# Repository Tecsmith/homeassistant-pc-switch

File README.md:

#  HA PC Switch

**Automate power on your PC using [ESPHome](https://github.com/esphome/esphome) or [Tasmota](https://github.com/arendst/Tasmota), and integrated into [Home Assistant](https://www.home-assistant.io/).**

## About

For more, visit the project page here: https://tecsmith.github.io/homeassistant-pc-switch/

## Assets:

* [Schematic PDF](docs/ha-pc-switch-revB.pdf)

---

Made with &#x1F499; by .

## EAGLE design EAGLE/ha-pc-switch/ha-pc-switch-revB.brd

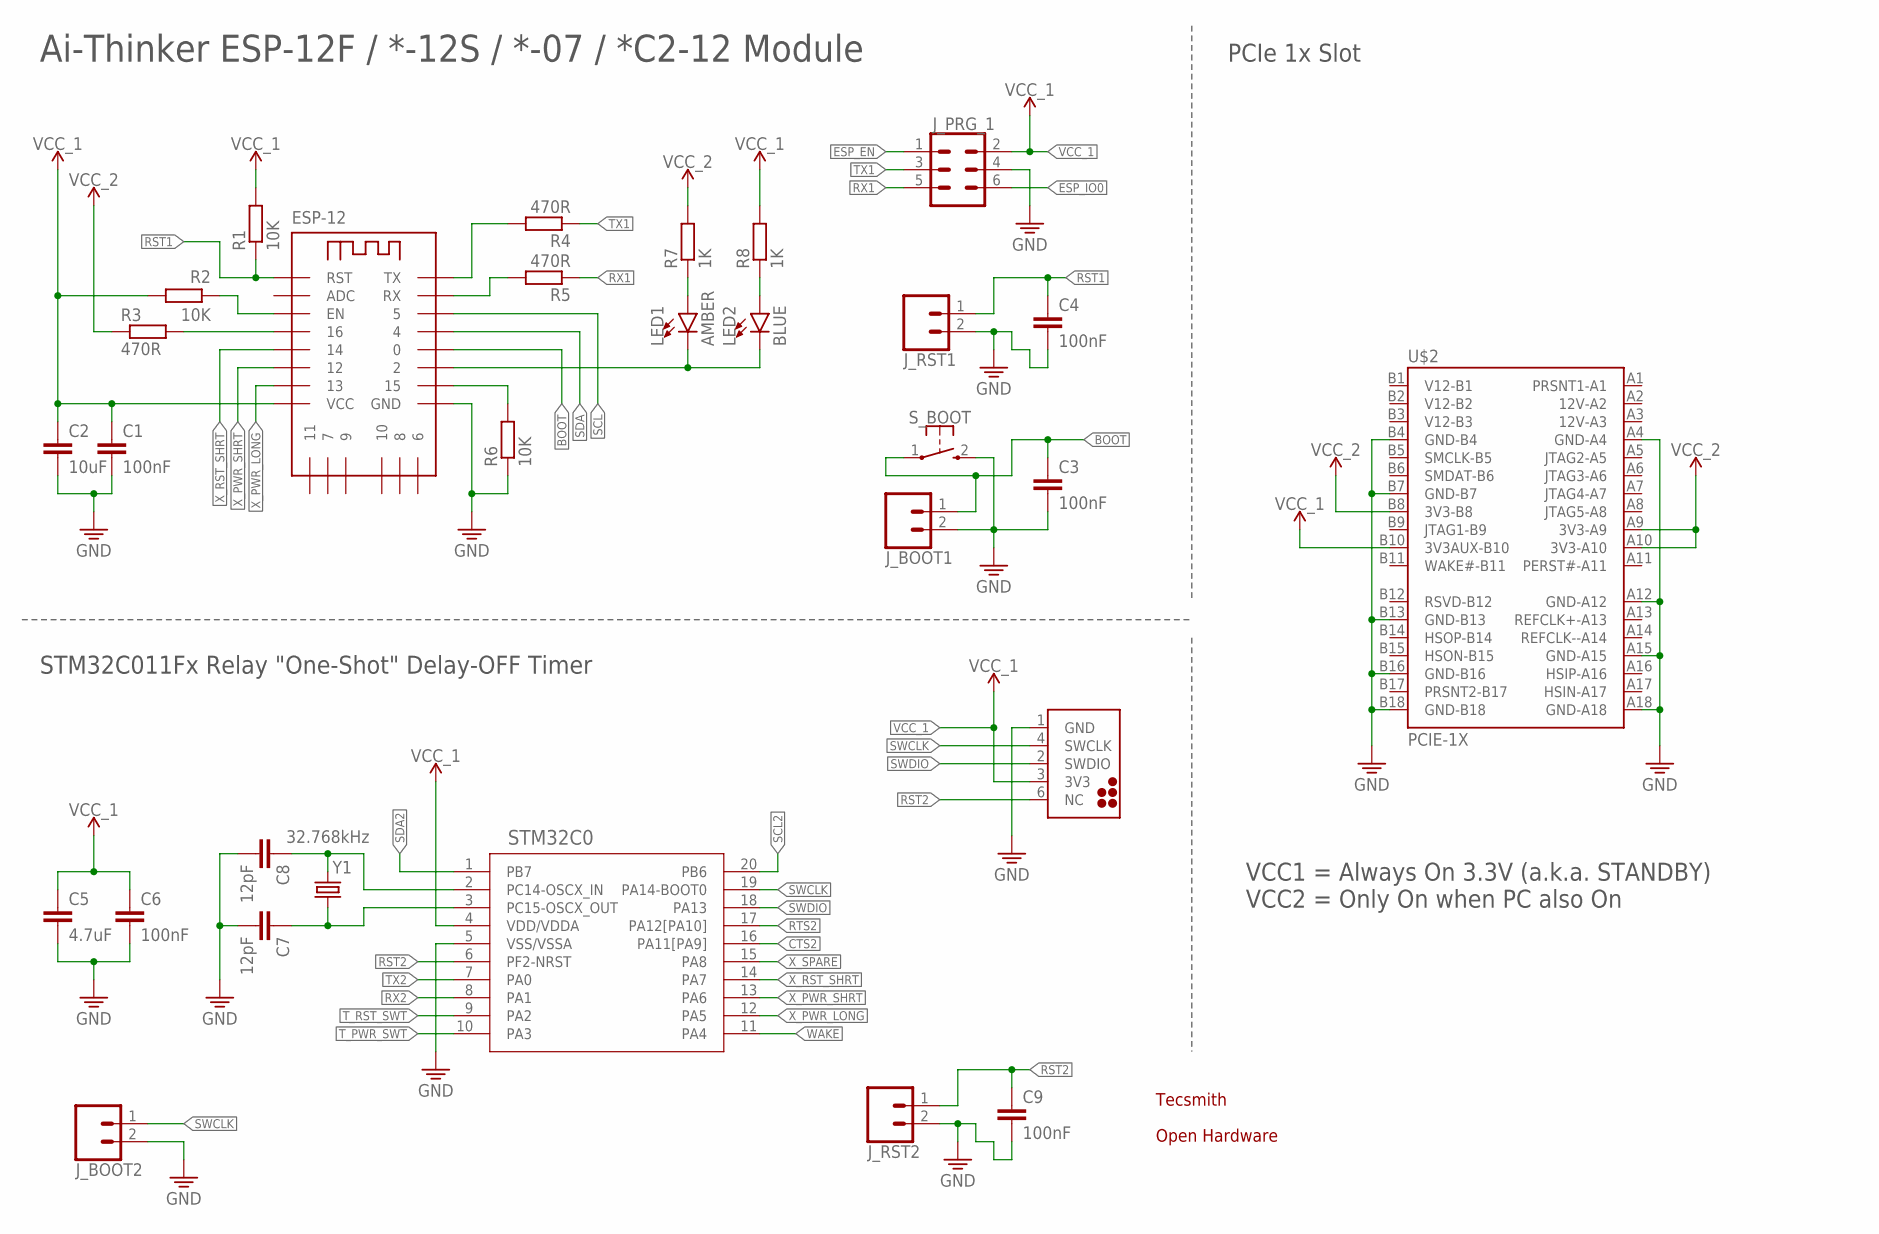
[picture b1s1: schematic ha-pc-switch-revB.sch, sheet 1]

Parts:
C1, C3, C4, C6, C9: 100nF; C0603
C2: 10uF; C0603
C5: 4.7uF; C0603
C7, C8: 12pF; C0603
ESP-12: ESPRESSIF-ESP-12F&ESMD; ESP8266-ESP-12E
J_BOOT1, J_BOOT2: CONN_021X02_NO_SILK; 1X02_NO_SILK
J_PRG2: NUCLEO_HEADER; NUCLEO
J_PRG_1: CONN_03X2NO_SILK; 2X3-NS
J_RST1, J_RST2: CONN_021X02_NO_SILK; 1X02_NO_SILK
LED1: AMBER; LED-0603
LED2: BLUE; LED-0603
LOGO1: OSHW-LOGOM; OSHW-LOGO-M
R1, R2, R6: 10K; R0603
R3, R4, R5: 470R; R0603
R7, R8: 1K; R0603
STM32C0: STM32C011FTSSOP20_STM-M; TSSOP20-M
S_BOOT: MOMENTARY-SWITCH-SPST-1; SKRKAEE020
U$1: TECSMITH-LOGOLONG; TECSMITH-NAME
U$2: PCIE-1X
Y1: 32.768kHz; CRYSTAL-SMD-3.2X1.5MM

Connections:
BOOT: C3.1, ESP-12.GPIO0 (0), J_BOOT1.1, S_BOOT.1
CTS2: STM32C0.16 (PA11[PA9])
ESP_EN: ESP-12.EN, J_PRG_1.1, R2.2
ESP_IO0: J_PRG_1.6
GND: C1.2, C2.2, C3.2, C4.2, C5.2, C6.2, C7.2, C8.2, C9.2, ESP-12.GND, J_BOOT1.2, J_BOOT2.2, J_PRG2.1 (GND), J_PRG_1.4, J_RST1.2, J_RST2.2, R6.1, STM32C0.5 (VSS/VSSA), S_BOOT.2 (3), U$2.A4 (GND-A4), U$2.A12 (GND-A12), U$2.A15 (GND-A15), U$2.A18 (GND-A18), U$2.B4 (GND-B4), U$2.B7 (GND-B7), U$2.B13 (GND-B13), U$2.B16 (GND-B16), U$2.B18 (GND-B18); also elsewhere on the board
unnamed: ESP-12.GPIO16 (16), R3.2
unnamed: LED2.A, R8.1
unnamed: C8.1, STM32C0.2 (PC14-OSCX_IN), Y1.P$2 (2)
unnamed: C7.1, STM32C0.3 (PC15-OSCX_OUT), Y1.P$1 (1)
unnamed: LED1.A, R7.1
unnamed: ESP-12.RXD0 (RX), R5.2
unnamed: ESP-12.GPIO2 (2), LED1.C, LED2.C
unnamed: ESP-12.TXD0 (TX), R4.2
unnamed: ESP-12.GPIO15 (15), R6.2
RST1: C4.1, ESP-12.RST, J_RST1.1, R1.1
RST2: C9.1, J_PRG2.6 (NC), J_RST2.1, STM32C0.6 (PF2-NRST)
RTS2: STM32C0.17 (PA12[PA10])
RX1: J_PRG_1.5, R5.1
RX2: STM32C0.8 (PA1)
SCL: ESP-12.GPIO5 (5); also elsewhere on the board
SCL2: STM32C0.20 (PB6)
SDA: ESP-12.GPIO4 (4); also elsewhere on the board
SDA2: STM32C0.1 (PB7)
SWCLK: J_BOOT2.1, J_PRG2.4 (SWCLK), STM32C0.19 (PA14-BOOT0)
SWDIO: J_PRG2.2 (SWDIO), STM32C0.18 (PA13)
TX1: J_PRG_1.3, R4.1
TX2: STM32C0.7 (PA0)
T_PWR_SWT: STM32C0.10 (PA3); also elsewhere on the board
T_RST_SWT: STM32C0.9 (PA2); also elsewhere on the board
VCC_1: C1.1, C2.1, C5.1, C6.1, ESP-12.VCC, J_PRG2.3 (3V3), J_PRG_1.2, R1.2, R2.1, R8.2, STM32C0.4 (VDD/VDDA), U$2.B10 (3V3AUX-B10); also elsewhere on the board
VCC_2: R3.1, R7.2, U$2.A9 (3V3-A9), U$2.A10 (3V3-A10), U$2.B8 (3V3-B8)
WAKE: STM32C0.11 (PA4)
X_PWR_LONG: ESP-12.GPIO13 (13), STM32C0.12 (PA5); also elsewhere on the board
X_PWR_SHRT: ESP-12.GPIO12 (12), STM32C0.13 (PA6); also elsewhere on the board
X_RST_SHRT: ESP-12.GPIO14 (14), STM32C0.14 (PA7); also elsewhere on the board
X_SPARE: STM32C0.15 (PA8)

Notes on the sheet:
Ai-Thinker ESP-12F / *-12S / *-07 / *C2-12 Module
STM32C011Fx Relay "One-Shot" Delay-OFF Timer
VCC1 = Always On 3.3V (a.k.a. STANDBY) VCC2 = Only On when PC also On
PCIe 1x Slot

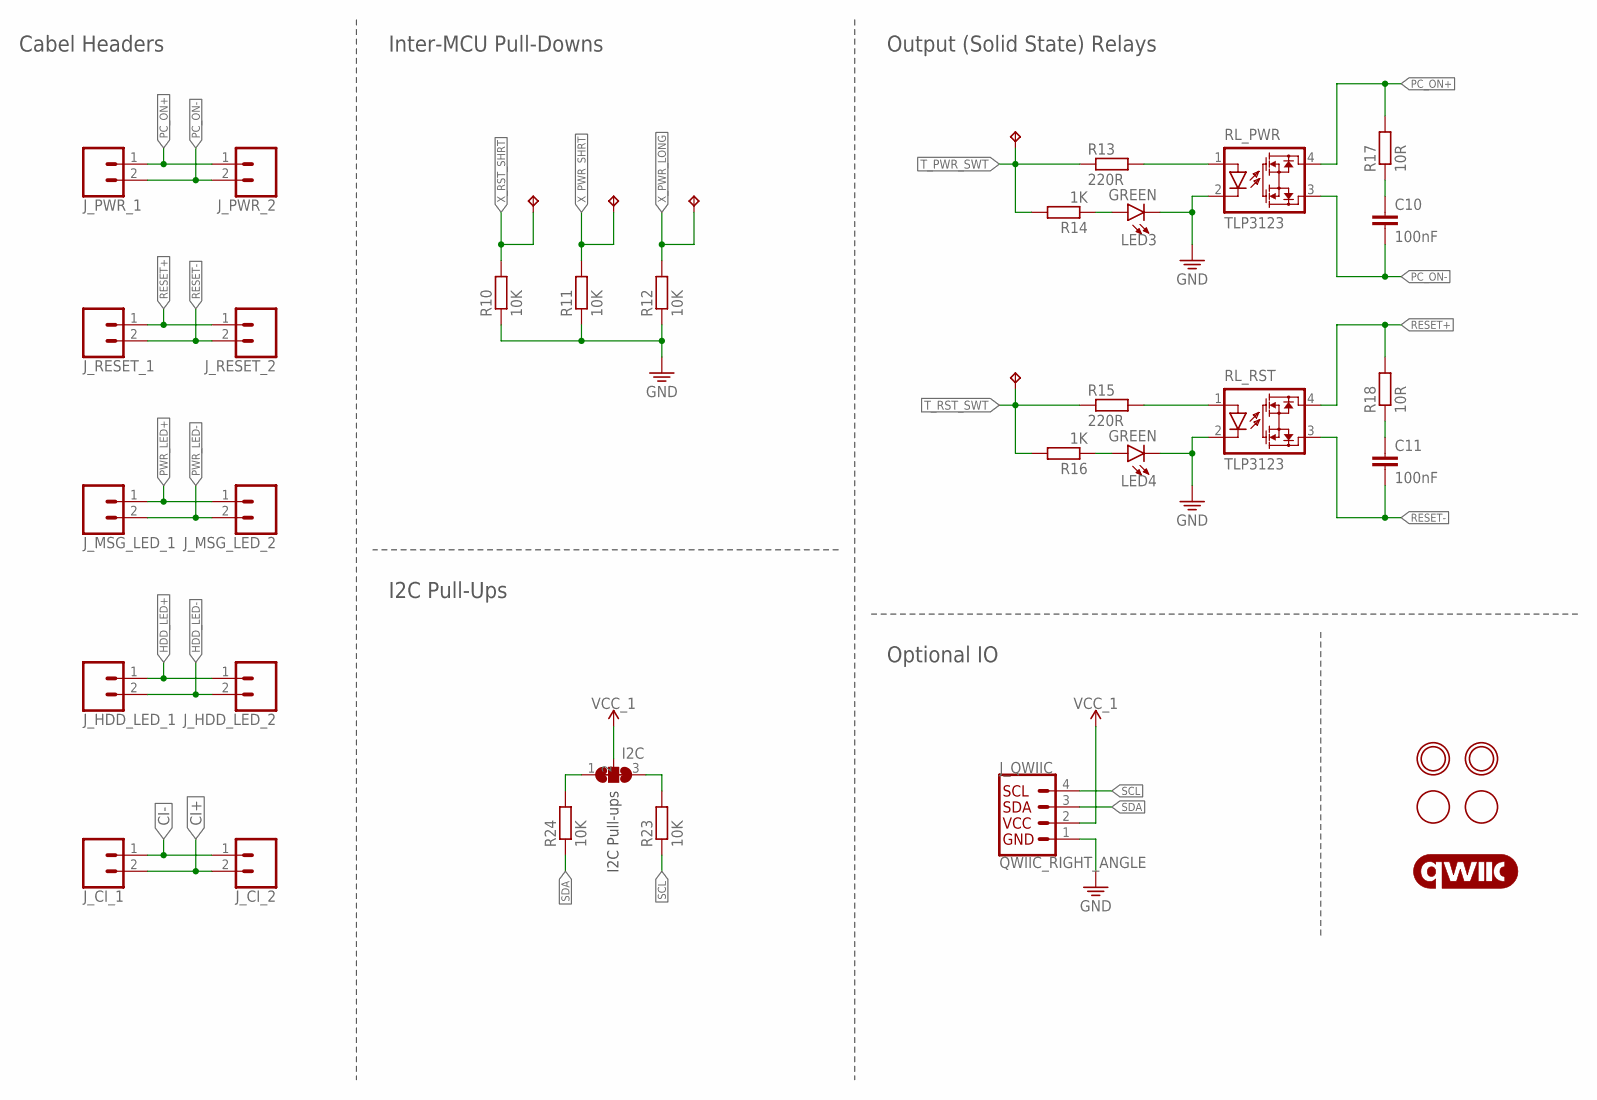
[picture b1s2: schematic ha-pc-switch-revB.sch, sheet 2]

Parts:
C10, C11: 100nF; C0603
I2C: JUMPER-1X3-CLOSED-2; SOLDERJUMPER_CLOSEDWIRE-3-2
J_CI_1, J_CI_2: CONN_021X02_NO_SILK; 1X02_NO_SILK
J_HDD_LED_1, J_HDD_LED_2: CONN_021X02_NO_SILK; 1X02_NO_SILK
J_MSG_LED_1, J_MSG_LED_2: CONN_021X02_NO_SILK; 1X02_NO_SILK
J_PWR_1, J_PWR_2: CONN_021X02_NO_SILK; 1X02_NO_SILK
J_QWIIC: QWIIC_RIGHT_ANGLE; JST04_1MM_RA
J_RESET_1, J_RESET_2: CONN_021X02_NO_SILK; 1X02_NO_SILK
LED3, LED4: GREEN; LED-0603
LOGO2: QWIIC_LOGO_4MM; QWIIC_4MM
R10, R11, R12, R23, R24: 10K; R0603
R13, R15: 220R; R0603
R14, R16: 1K; R0603
R17, R18: 10R; R0603
RL_PWR: TLP3123; SOP4_TOS
RL_RST: TLP3123; SOP4_TOS
TP6, TP7, TP8, TP9, TP10: TPTP16SQ; TP16SQ
U$9, U$11: MOUNTINGHOLE3.0THIN; MOUNTINGHOLE_3.0_PLATEDTHIN
U$15, U$16: FIDUCIAL; FIDUCIAL_1MM

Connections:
CI+: J_CI_1.2, J_CI_2.2
CI-: J_CI_1.1, J_CI_2.1
GND: J_QWIIC.1, LED3.C, LED4.C, R10.1, R11.1, R12.1, RL_PWR.2 (C), RL_RST.2 (C); also elsewhere on the board
HDD_LED+: J_HDD_LED_1.1, J_HDD_LED_2.1
HDD_LED-: J_HDD_LED_1.2, J_HDD_LED_2.2
unnamed: R15.2, RL_RST.1 (A)
unnamed: C10.1, R17.1
unnamed: C11.1, R18.1
unnamed: R13.2, RL_PWR.1 (A)
unnamed: LED3.A, R14.1
unnamed: I2C.3, R23.2
unnamed: I2C.1, R24.2
unnamed: LED4.A, R16.1
PC_ON+: J_PWR_1.1, J_PWR_2.1, R17.2, RL_PWR.4 (D1)
PC_ON-: C10.2, J_PWR_1.2, J_PWR_2.2, RL_PWR.3 (D2)
PWR_LED+: J_MSG_LED_1.1, J_MSG_LED_2.1
PWR_LED-: J_MSG_LED_1.2, J_MSG_LED_2.2
RESET+: J_RESET_1.1, J_RESET_2.1, R18.2, RL_RST.4 (D1)
RESET-: C11.2, J_RESET_1.2, J_RESET_2.2, RL_RST.3 (D2)
SCL: J_QWIIC.4, R23.1; also elsewhere on the board
SDA: J_QWIIC.3, R24.1; also elsewhere on the board
T_PWR_SWT: R13.1, R14.2, TP9.TP; also elsewhere on the board
T_RST_SWT: R15.1, R16.2, TP10.TP; also elsewhere on the board
VCC_1: I2C.2, J_QWIIC.2; also elsewhere on the board
X_PWR_LONG: R12.2, TP8.TP; also elsewhere on the board
X_PWR_SHRT: R11.2, TP7.TP; also elsewhere on the board
X_RST_SHRT: R10.2, TP6.TP; also elsewhere on the board

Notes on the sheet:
Cabel Headers
Output (Solid State) Relays
Optional IO
I2C Pull-ups
Inter-MCU Pull-Downs
I2C Pull-Ups

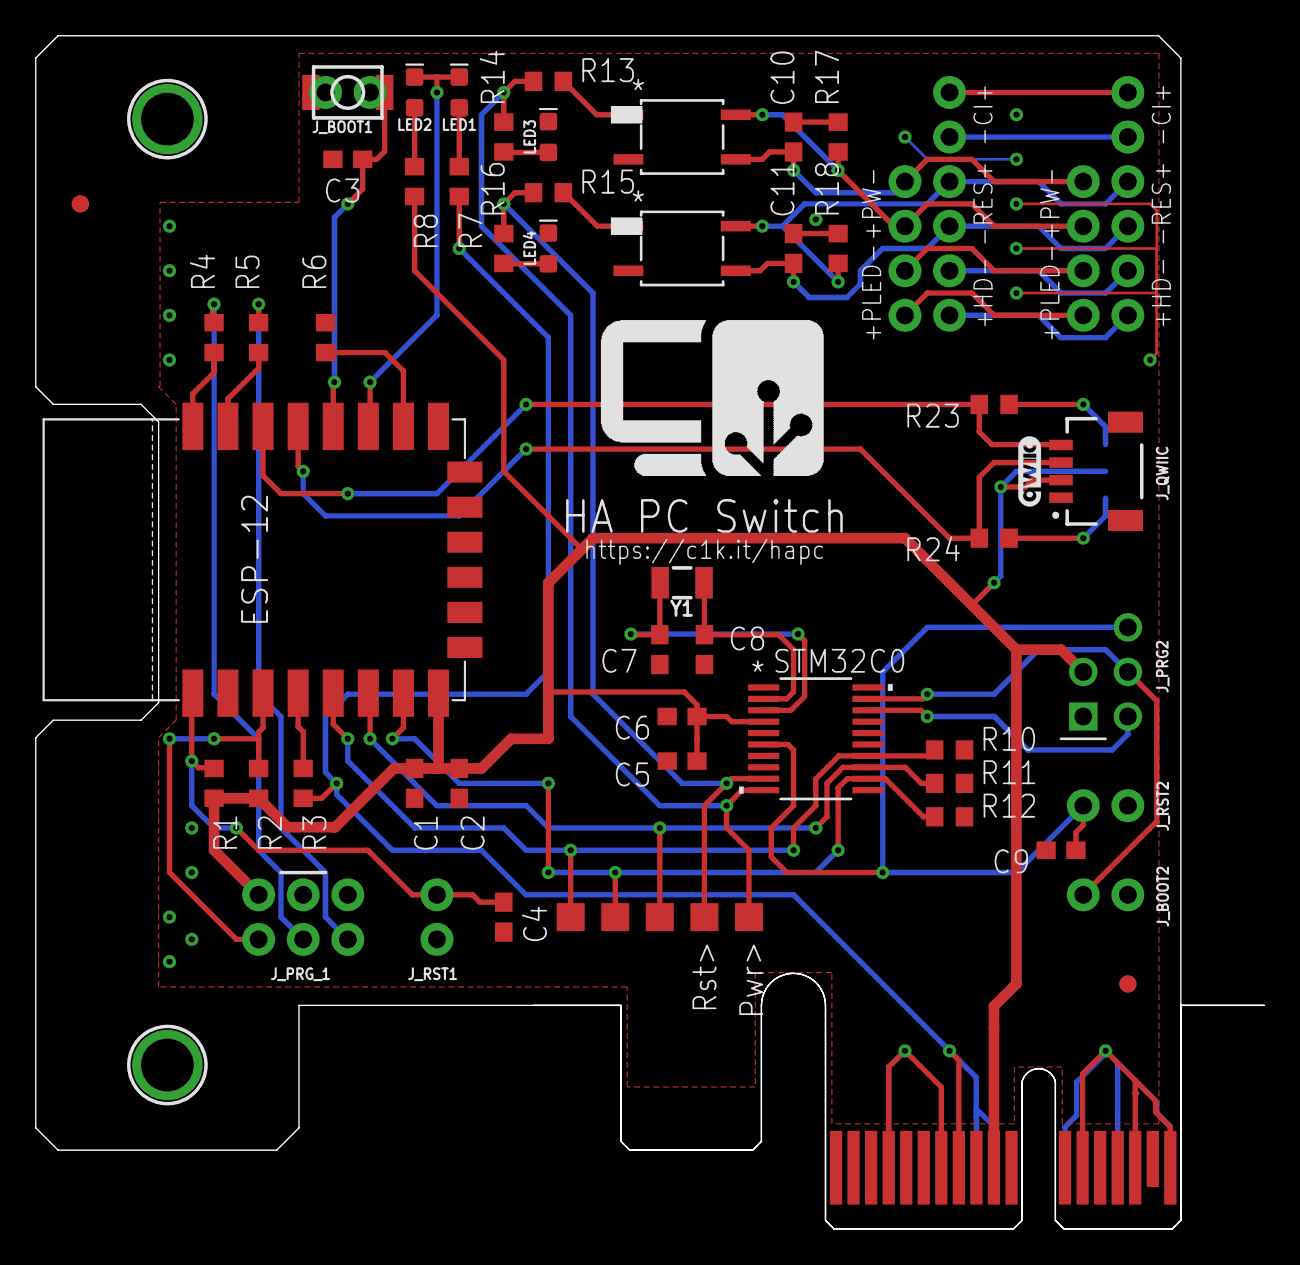
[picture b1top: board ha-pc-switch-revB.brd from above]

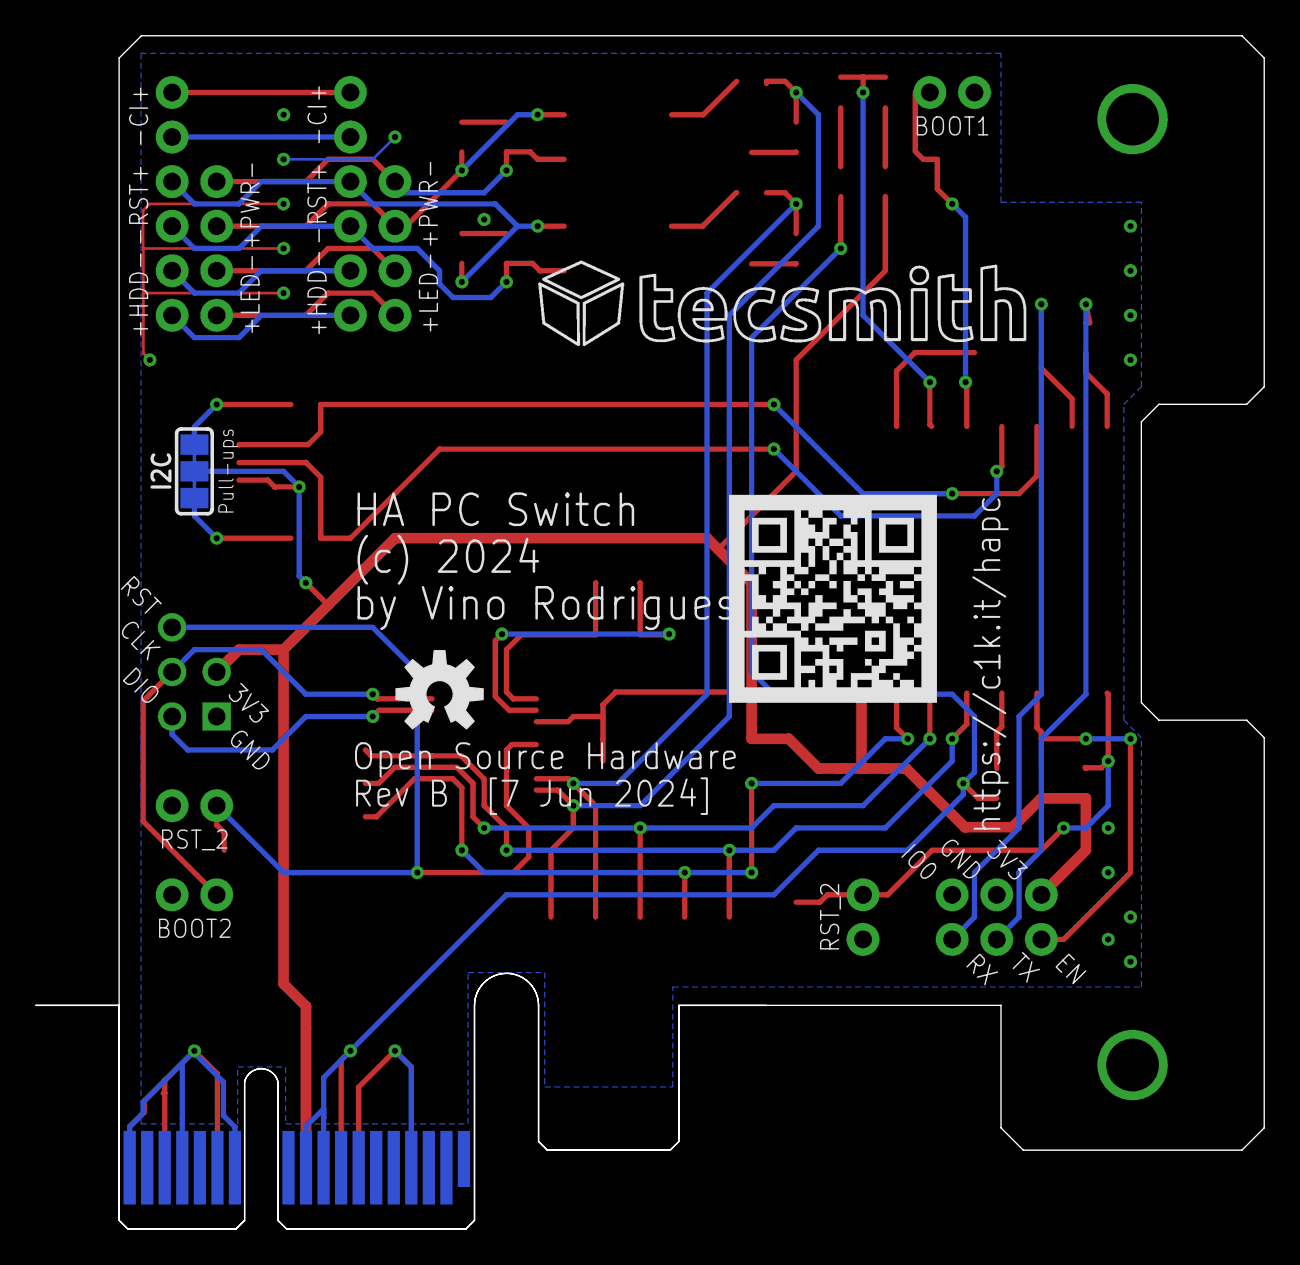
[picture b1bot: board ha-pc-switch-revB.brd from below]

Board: 2 copper layers, 70.0 x 68.0 mm, 71 parts (3 on the bottom side), 45 nets.

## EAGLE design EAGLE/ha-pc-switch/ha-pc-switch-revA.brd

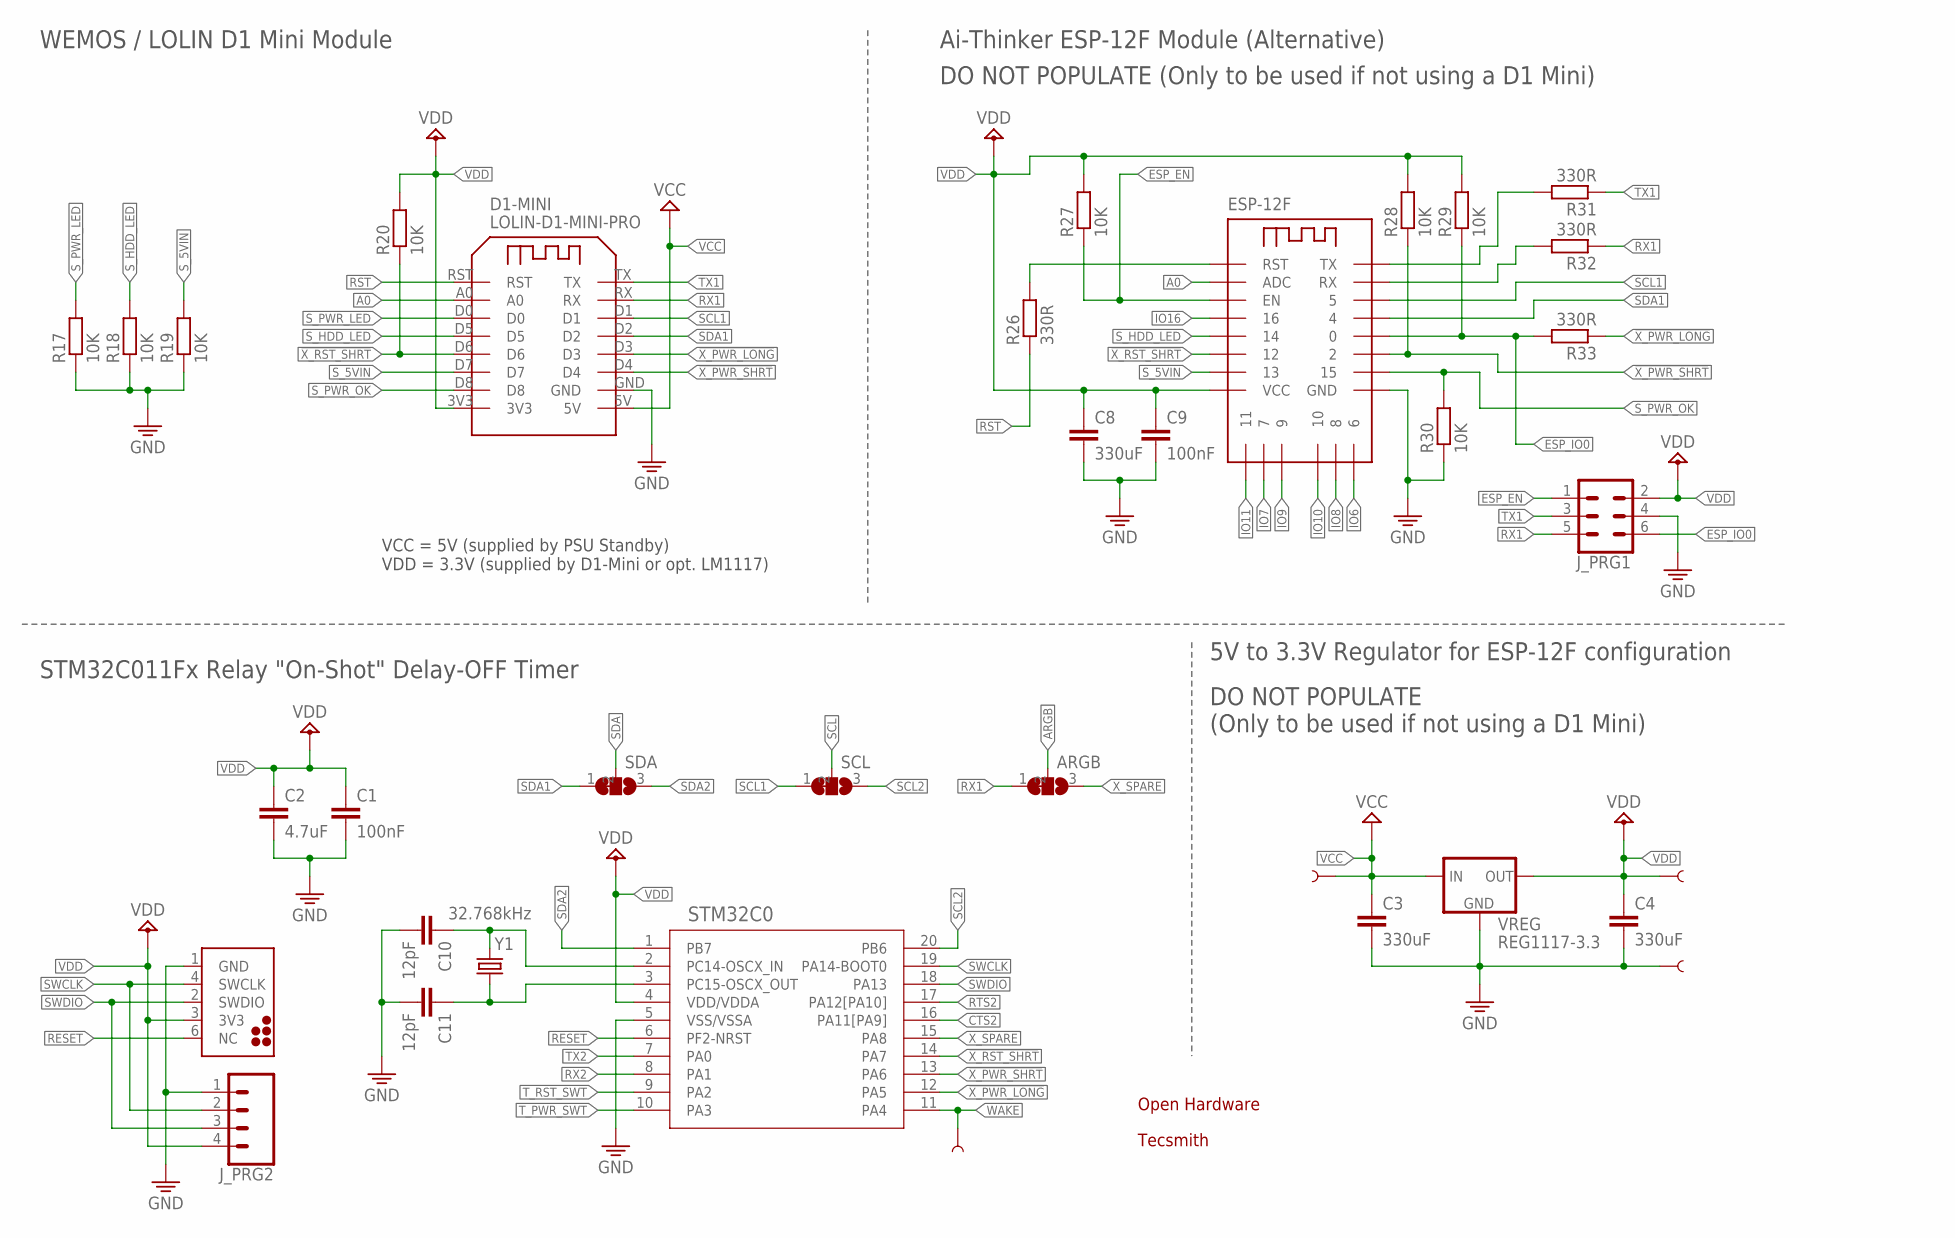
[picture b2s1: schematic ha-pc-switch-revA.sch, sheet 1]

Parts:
ARGB: JUMPER-1X3-CLOSED; SOLDERJUMPER_CLOSEDWIRE-3
C1, C9: 100nF; C0603
C2: 4.7uF; C0603
C3, C4, C8: 330uF; C0603
C10, C11: 12pF; C0603
D1-MINI: LOLIN-D1-MINI-PRO; WEMOS-D1-MINI-PRO
ESP-12F: ESPRESSIF-ESP-12F&ESMD; ESP8266-ESP-12E
J_DBG2: NUCLEO_HEADER; NUCLEO
J_PRG1: CONN_03X2FEMALE_SMD; 2X3_SMD
J_PRG2: 1X04_SMD_STRAIGHT_COMBO; 1X04_SMD_VERTICAL_COMBO
LOGO1: OSHW-LOGOM; OSHW-LOGO-M
R17, R18, R19, R20, R27, R28, R29, R30: 10K; R0603
R26, R31, R32, R33: 330R; R0603
SCL: JUMPER-1X3-CLOSED; SOLDERJUMPER_CLOSEDWIRE-3
SDA: JUMPER-1X3-CLOSED; SOLDERJUMPER_CLOSEDWIRE-3
STM32C0: STM32C011FTSSOP20_STM-M; TSSOP20-M
TP1, TP2, TP3, TP4: TEST-POINT3X5; PAD.03X.05
U$1: TECSMITH-LOGOLONG; TECSMITH-NAME
VREG: REG1117-3.3; SOT223
Y1: 32.768kHz; CRYSTAL-SMD-3.2X1.5MM

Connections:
!X_PWR_LONG: D1-MINI.D3, R33.1, STM32C0.12 (PA5)
!X_PWR_SHRT: D1-MINI.D4, ESP-12F.GPIO2 (2), R28.1, STM32C0.13 (PA6)
!X_RST_SHRT: D1-MINI.D6, ESP-12F.GPIO12 (12), R20.1, STM32C0.14 (PA7)
A0: D1-MINI.A0, ESP-12F.ADC0 (ADC); also elsewhere on the board
ARGB: ARGB.2; also elsewhere on the board
CTS2: STM32C0.16 (PA11[PA9])
ESP_EN: ESP-12F.EN, J_PRG1.1, R27.1
ESP_IO0: ESP-12F.GPIO0 (0), J_PRG1.6, R29.1, R33.2
GND: C1.2, C2.2, C3.2, C4.2, C8.2, C9.2, C10.2, C11.2, D1-MINI.GND, ESP-12F.GND, J_DBG2.1 (GND), J_PRG1.4, J_PRG2.1, R17.1, R18.1, R19.1, R30.1, STM32C0.5 (VSS/VSSA), TP3.1, VREG.1 (GND); also elsewhere on the board
IO6: ESP-12F.SCLK (6); also elsewhere on the board
IO7: ESP-12F.MISO (7); also elsewhere on the board
IO8: ESP-12F.MOSI (8); also elsewhere on the board
IO9: ESP-12F.GPIO9 (9); also elsewhere on the board
IO10: ESP-12F.GPIO10 (10); also elsewhere on the board
IO11: ESP-12F.CS0 (11); also elsewhere on the board
IO16: ESP-12F.GPIO16 (16)
unnamed: C10.1, STM32C0.2 (PC14-OSCX_IN), Y1.P$2 (2)
unnamed: C11.1, STM32C0.3 (PC15-OSCX_OUT), Y1.P$1 (1)
unnamed: ESP-12F.RST, R26.2
unnamed: ESP-12F.RXD0 (RX), R32.2
unnamed: ESP-12F.TXD0 (TX), R31.2
RESET: J_DBG2.6 (NC), STM32C0.6 (PF2-NRST)
RST: D1-MINI.RST, R26.1; also elsewhere on the board
RTS2: STM32C0.17 (PA12[PA10])
RX1: ARGB.1, D1-MINI.RX, J_PRG1.5, R32.1
RX2: STM32C0.8 (PA1)
SCL: SCL.2; also elsewhere on the board
SCL1: D1-MINI.D1, ESP-12F.GPIO5 (5), SCL.1
SCL2: SCL.3, STM32C0.20 (PB6)
SDA: SDA.2; also elsewhere on the board
SDA1: D1-MINI.D2, ESP-12F.GPIO4 (4), SDA.1
SDA2: SDA.3, STM32C0.1 (PB7)
SWCLK: J_DBG2.4 (SWCLK), J_PRG2.2, STM32C0.19 (PA14-BOOT0)
SWDIO: J_DBG2.2 (SWDIO), J_PRG2.3, STM32C0.18 (PA13)
S_5VIN: D1-MINI.D7, ESP-12F.GPIO13 (13), R19.2; also elsewhere on the board
S_HDD_LED: D1-MINI.D5, ESP-12F.GPIO14 (14), R18.2; also elsewhere on the board
S_PWR_LED: D1-MINI.D0, R17.2; also elsewhere on the board
S_PWR_OK: D1-MINI.D8, ESP-12F.GPIO15 (15), R30.2; also elsewhere on the board
TX1: D1-MINI.TX, J_PRG1.3, R31.1
TX2: STM32C0.7 (PA0)
T_PWR_SWT: STM32C0.10 (PA3); also elsewhere on the board
T_RST_SWT: STM32C0.9 (PA2); also elsewhere on the board
VCC: C3.1, D1-MINI.5V, TP1.1, VREG.3 (IN); also elsewhere on the board
VDD: C1.1, C2.1, C4.1, C8.1, C9.1, D1-MINI.3V3, ESP-12F.VCC, J_DBG2.3 (3V3), J_PRG1.2, J_PRG2.4, R20.2, R27.2, R28.2, R29.2, STM32C0.4 (VDD/VDDA), TP2.1, VREG.2 (OUT), VREG.T (OUT); also elsewhere on the board
WAKE: STM32C0.11 (PA4), TP4.1
X_SPARE: ARGB.3, STM32C0.15 (PA8)

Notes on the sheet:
WEMOS / LOLIN D1 Mini Module
Ai-Thinker ESP-12F Module (Alternative)
STM32C011Fx Relay "On-Shot" Delay-OFF Timer
DO NOT POPULATE (Only to be used if not using a D1 Mini)
5V to 3.3V Regulator for ESP-12F configuration
DO NOT POPULATE (Only to be used if not using a D1 Mini)
VCC = 5V (supplied by PSU Standby) VDD = 3.3V (supplied by D1-Mini or opt. LM1117)

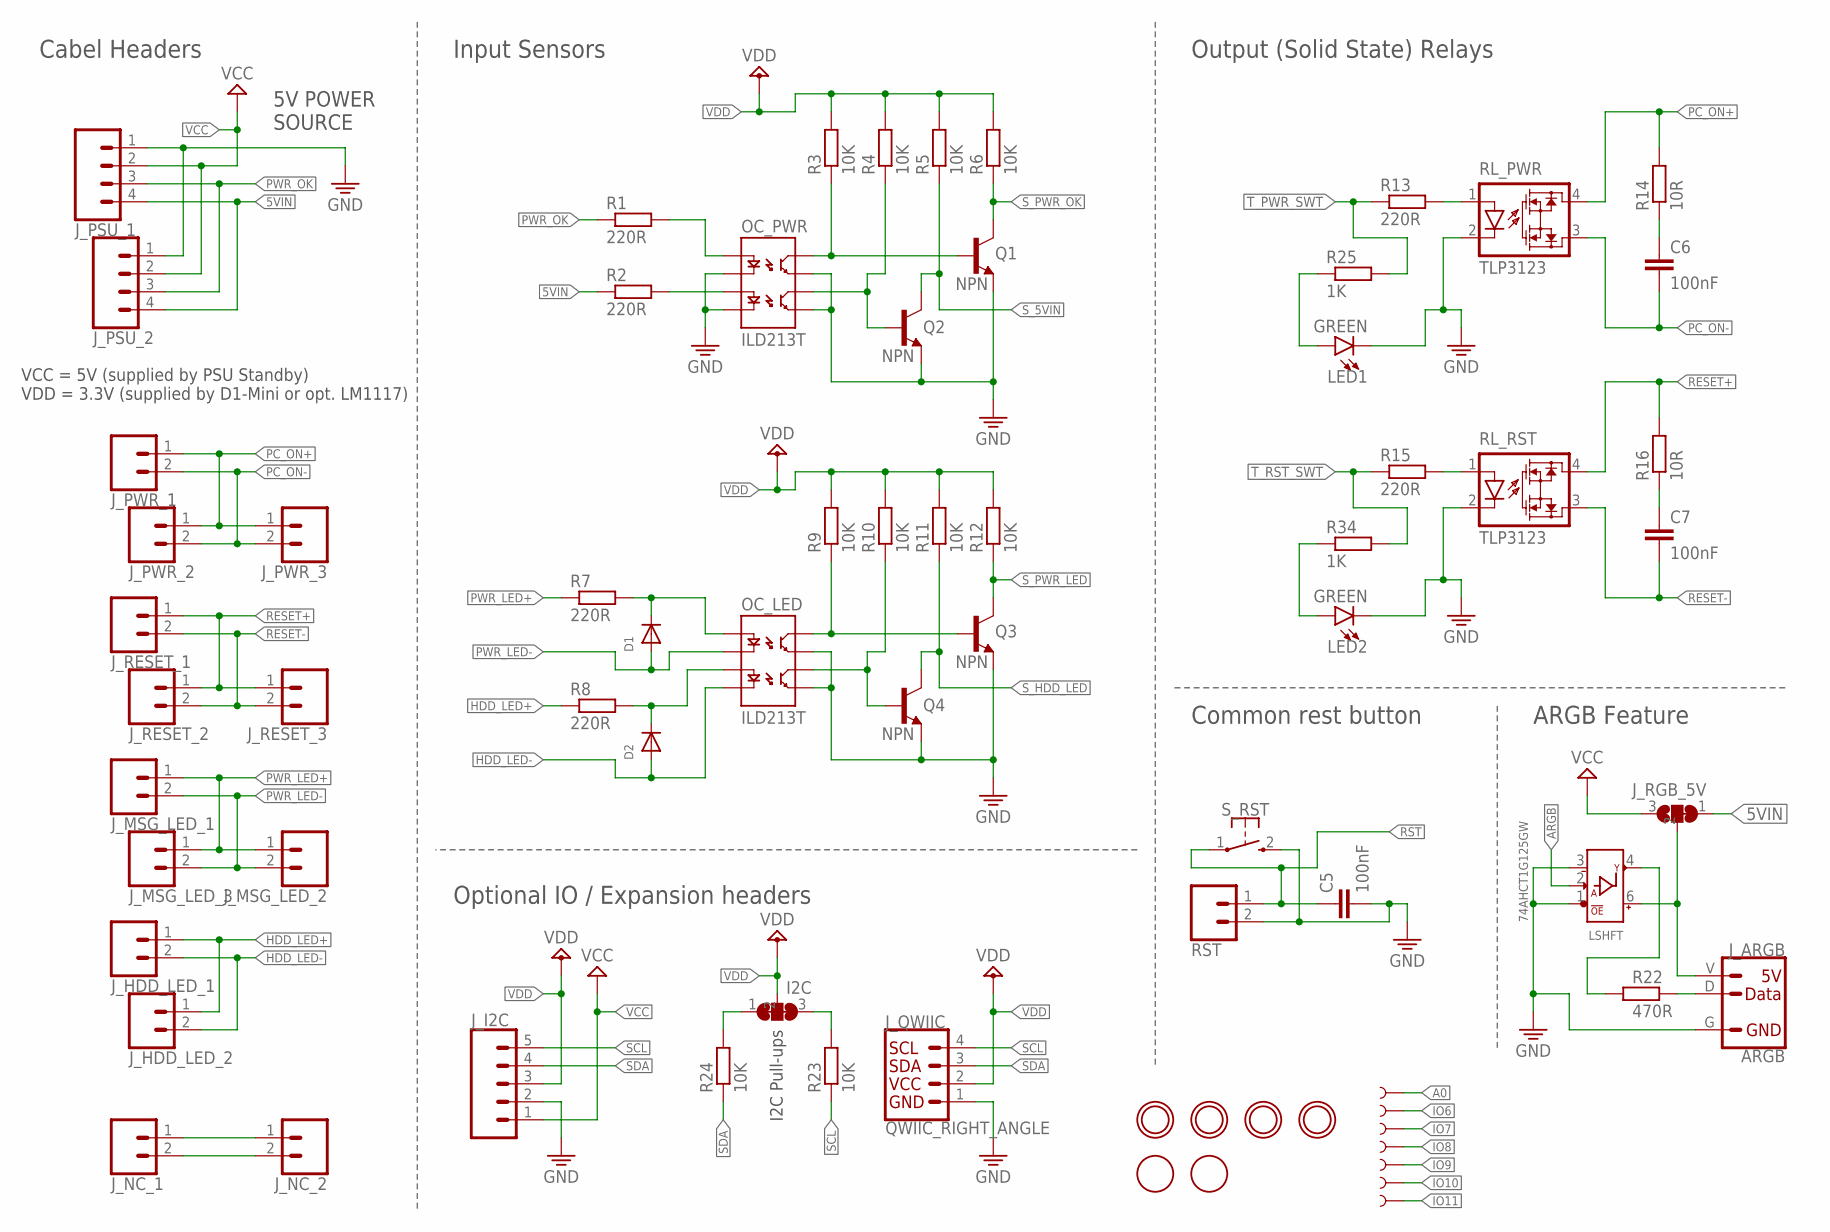
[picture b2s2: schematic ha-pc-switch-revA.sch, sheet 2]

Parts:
C5, C6, C7: 100nF; C0603
D1, D2: DIODESOD-523; SOD-523
I2C: JUMPER-1X3-CLOSED-2; SOLDERJUMPER_CLOSEDWIRE-3-2
J_ARGB: ARGB
J_HDD_LED_1, J_HDD_LED_2: CONN_021X02_NO_SILK; 1X02_NO_SILK
J_I2C: CONN_05SCREW; SCREWTERMINAL-3.5MM-5
J_MSG_LED_1, J_MSG_LED_2: CONN_021X02_NO_SILK; 1X02_NO_SILK
J_MSG_LED_3: CONN_02PTH3; 1X02_LONGPADS
J_NC_1, J_NC_2: CONN_021X02_NO_SILK; 1X02_NO_SILK
J_PSU_1: CONN_04LONGPADS; 1X04_LONGPADS
J_PSU_2: CONN_04SCREW; SCREWTERMINAL-3.5MM-4
J_PWR_1, J_PWR_2: CONN_021X02_NO_SILK; 1X02_NO_SILK
J_PWR_3: CONN_02PTH3; 1X02_LONGPADS
J_QWIIC: QWIIC_RIGHT_ANGLE; JST04_1MM_RA
J_RESET_1, J_RESET_2: CONN_021X02_NO_SILK; 1X02_NO_SILK
J_RESET_3: CONN_02PTH3; 1X02_LONGPADS
J_RGB_5V: JUMPER-1X3-CLOSEDPINS; 1X03_ROUND_CLOSED
LED1, LED2: GREEN; LED-0603
LSHFT: 74AHCT1G125GW; SC-88A__TSSOP5__SOT353-1
OC_LED: ILD213T; SO08-2
OC_PWR: ILD213T; SO08-2
Q1, Q2, Q3, Q4: NPN; SOT23-3
R1, R2, R7, R8, R13, R15: 220R; R0603
R3, R4, R5, R6, R9, R10, R11, R12, R23, R24: 10K; R0603
R14, R16: 10R; R0603
R22: 470R; R0603
R25, R34: 1K; R0603
RL_PWR: TLP3123; SOP4_TOS
RL_RST: TLP3123; SOP4_TOS
RST: CONN_021X02_NO_SILK; 1X02_NO_SILK
S_RST: MOMENTARY-SWITCH-SPST-1; SKRKAEE020
TP9, TP10, TP11, TP12, TP14, TP15, TP16: TEST-POINT3X5; PAD.03X.05
U$5, U$9, U$11, U$12: MOUNTINGHOLE3.0THIN; MOUNTINGHOLE_3.0_PLATEDTHIN
U$15, U$16: FIDUCIAL; FIDUCIAL_1MM

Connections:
5VIN: J_PSU_1.4, J_PSU_2.4, J_RGB_5V.1, R2.1
A0: TP12.1; also elsewhere on the board
ARGB: LSHFT.2 (A_DIN); also elsewhere on the board
GND: C5.2, J_ARGB.G, J_I2C.2, J_PSU_1.1, J_PSU_2.1, J_QWIIC.1, LED1.C, LED2.C, LSHFT.1 (!OE), LSHFT.3 (3_GND), OC_LED.5 (EM2), OC_LED.7 (EM1), OC_PWR.2 (C1), OC_PWR.4 (C2), OC_PWR.5 (EM2), OC_PWR.7 (EM1), Q1.2 (E), Q2.2 (E), Q3.2 (E), Q4.2 (E), RL_PWR.2 (C), RL_RST.2 (C), RST.2, S_RST.2 (3); also elsewhere on the board
HDD_LED+: J_HDD_LED_1.1, J_HDD_LED_2.1, R8.1
HDD_LED-: D2.A, J_HDD_LED_1.2, J_HDD_LED_2.2, OC_LED.4 (C2)
IO6: TP11.1; also elsewhere on the board
IO7: TP10.1; also elsewhere on the board
IO8: TP9.1; also elsewhere on the board
IO9: TP16.1; also elsewhere on the board
IO10: TP15.1; also elsewhere on the board
IO11: TP14.1; also elsewhere on the board
unnamed: OC_PWR.1 (A1), R1.2
unnamed: OC_PWR.3 (A2), R2.2
unnamed: J_NC_1.1, J_NC_2.1
unnamed: J_NC_1.2, J_NC_2.2
unnamed: R15.2, RL_RST.1 (A)
unnamed: D2.K (C), OC_LED.3 (A2), R8.2
unnamed: C6.1, R14.1
unnamed: C7.1, R16.1
unnamed: R13.2, RL_PWR.1 (A)
unnamed: J_ARGB.V, J_RGB_5V.2, LSHFT.6 (5_VCC)
unnamed: D1.K (C), OC_LED.1 (A1), R7.2
unnamed: LSHFT.4 (Y_DOUT), R22.1
unnamed: J_ARGB.D, R22.2
unnamed: LED1.A, R25.1
unnamed: I2C.3, R23.2
unnamed: I2C.1, R24.2
unnamed: LED2.A, R34.1
OUT1N: OC_PWR.8 (CL1), Q1.1 (B), R3.1
OUT1N1: OC_LED.8 (CL1), Q3.1 (B), R9.1
OUT2N: OC_PWR.6 (CL2), Q2.1 (B), R4.1
OUT2N1: OC_LED.6 (CL2), Q4.1 (B), R10.1
PC_ON+: J_PWR_1.1, J_PWR_2.1, J_PWR_3.1, R14.2, RL_PWR.4 (D1)
PC_ON-: C6.2, J_PWR_1.2, J_PWR_2.2, J_PWR_3.2, RL_PWR.3 (D2)
PWR_LED+: J_MSG_LED_1.1, J_MSG_LED_2.1, J_MSG_LED_3.1, R7.1
PWR_LED-: D1.A, J_MSG_LED_1.2, J_MSG_LED_2.2, J_MSG_LED_3.2, OC_LED.2 (C1)
PWR_OK: J_PSU_1.3, J_PSU_2.3, R1.1
RESET+: J_RESET_1.1, J_RESET_2.1, J_RESET_3.1, R16.2, RL_RST.4 (D1)
RESET-: C7.2, J_RESET_1.2, J_RESET_2.2, J_RESET_3.2, RL_RST.3 (D2)
RST: C5.1, RST.1, S_RST.1; also elsewhere on the board
SCL: J_I2C.5, J_QWIIC.4, R23.1; also elsewhere on the board
SDA: J_I2C.4, J_QWIIC.3, R24.1; also elsewhere on the board
S_5VIN: Q2.3 (C), R5.1; also elsewhere on the board
S_HDD_LED: Q4.3 (C), R11.1; also elsewhere on the board
S_PWR_LED: Q3.3 (C), R12.1; also elsewhere on the board
S_PWR_OK: Q1.3 (C), R6.1; also elsewhere on the board
T_PWR_SWT: R13.1, R25.2; also elsewhere on the board
T_RST_SWT: R15.1, R34.2; also elsewhere on the board
VCC: J_I2C.1, J_PSU_1.2, J_PSU_2.2, J_RGB_5V.3; also elsewhere on the board
VDD: I2C.2, J_I2C.3, J_QWIIC.2, R3.2, R4.2, R5.2, R6.2, R9.2, R10.2, R11.2, R12.2; also elsewhere on the board

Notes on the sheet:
Cabel Headers
Input Sensors
Output (Solid State) Relays
Optional IO / Expansion headers
Common rest button
VCC = 5V (supplied by PSU Standby) VDD = 3.3V (supplied by D1-Mini or opt. LM1117)
5V POWER SOURCE
ARGB Feature
I2C Pull-ups

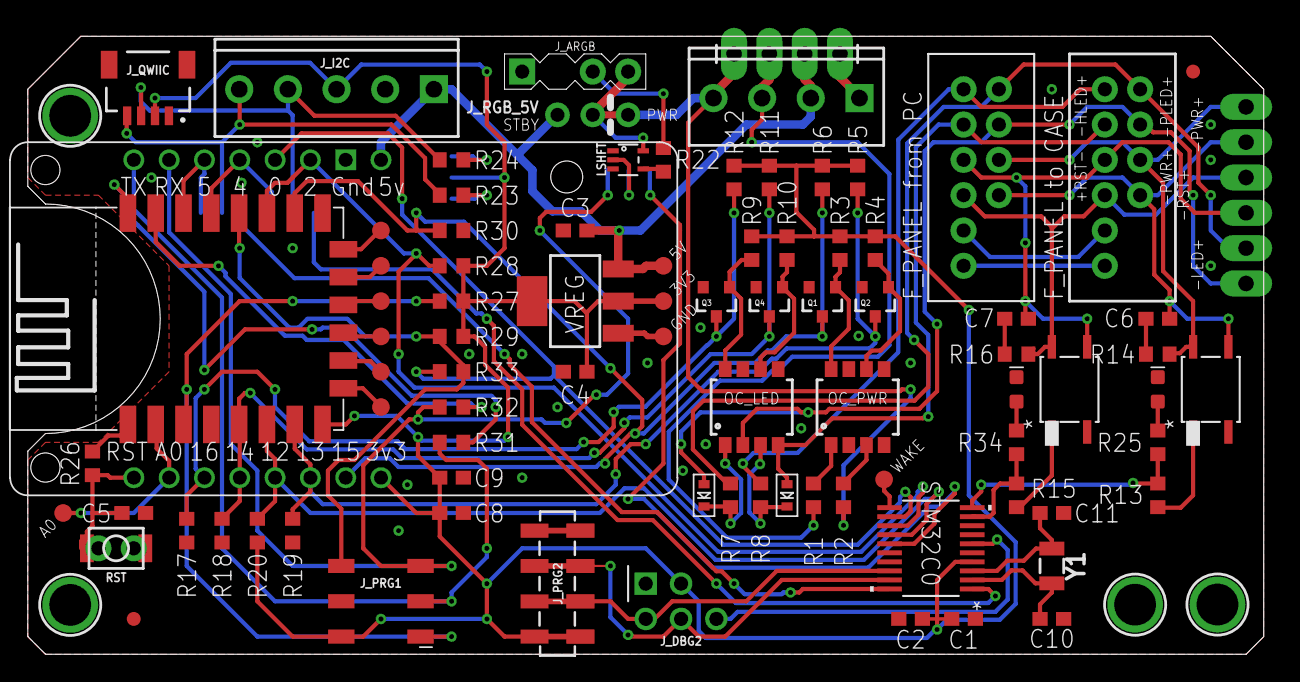
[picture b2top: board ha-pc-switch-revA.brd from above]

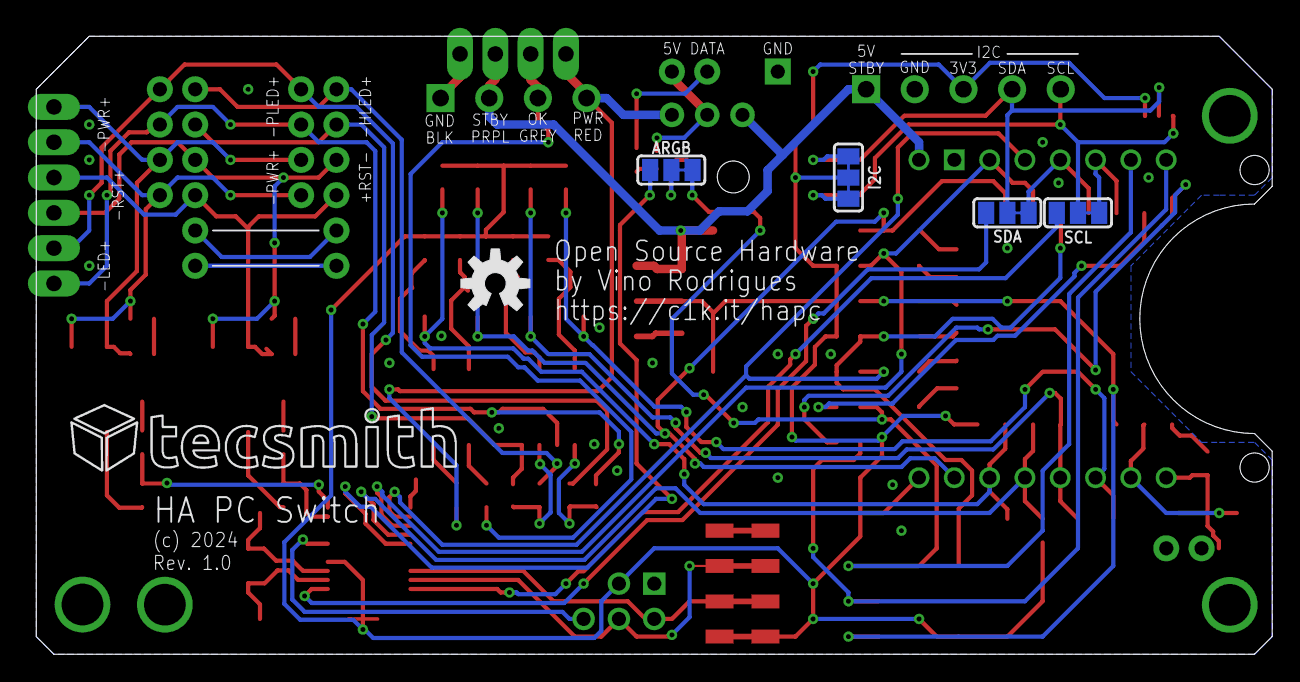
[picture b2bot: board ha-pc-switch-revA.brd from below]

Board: 2 copper layers, 88.9 x 44.4 mm, 109 parts (6 on the bottom side), 72 nets.

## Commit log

2024-05-02 initial DOCs / Pages upload
2024-05-02 initial ideation phase
2024-05-04 added esp-12f
2024-05-05 Revert "x"
    This reverts commit 2a8bda318214b1478a6d55f1f6b11f3f88d18c3c.
2024-05-05 EAGLE sch's
2024-06-02 pcb routed
2024-06-07 Rev B

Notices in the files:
parts and their libraries:
SparkFun-Connectors: Licensing: Creative Commons ShareAlike 4.0 International - https://creativecommons.org/licenses/by-sa/4.0
COPYRIGHT: Copyright (C) 2024 Ultra Librarian. All rights reserved.
